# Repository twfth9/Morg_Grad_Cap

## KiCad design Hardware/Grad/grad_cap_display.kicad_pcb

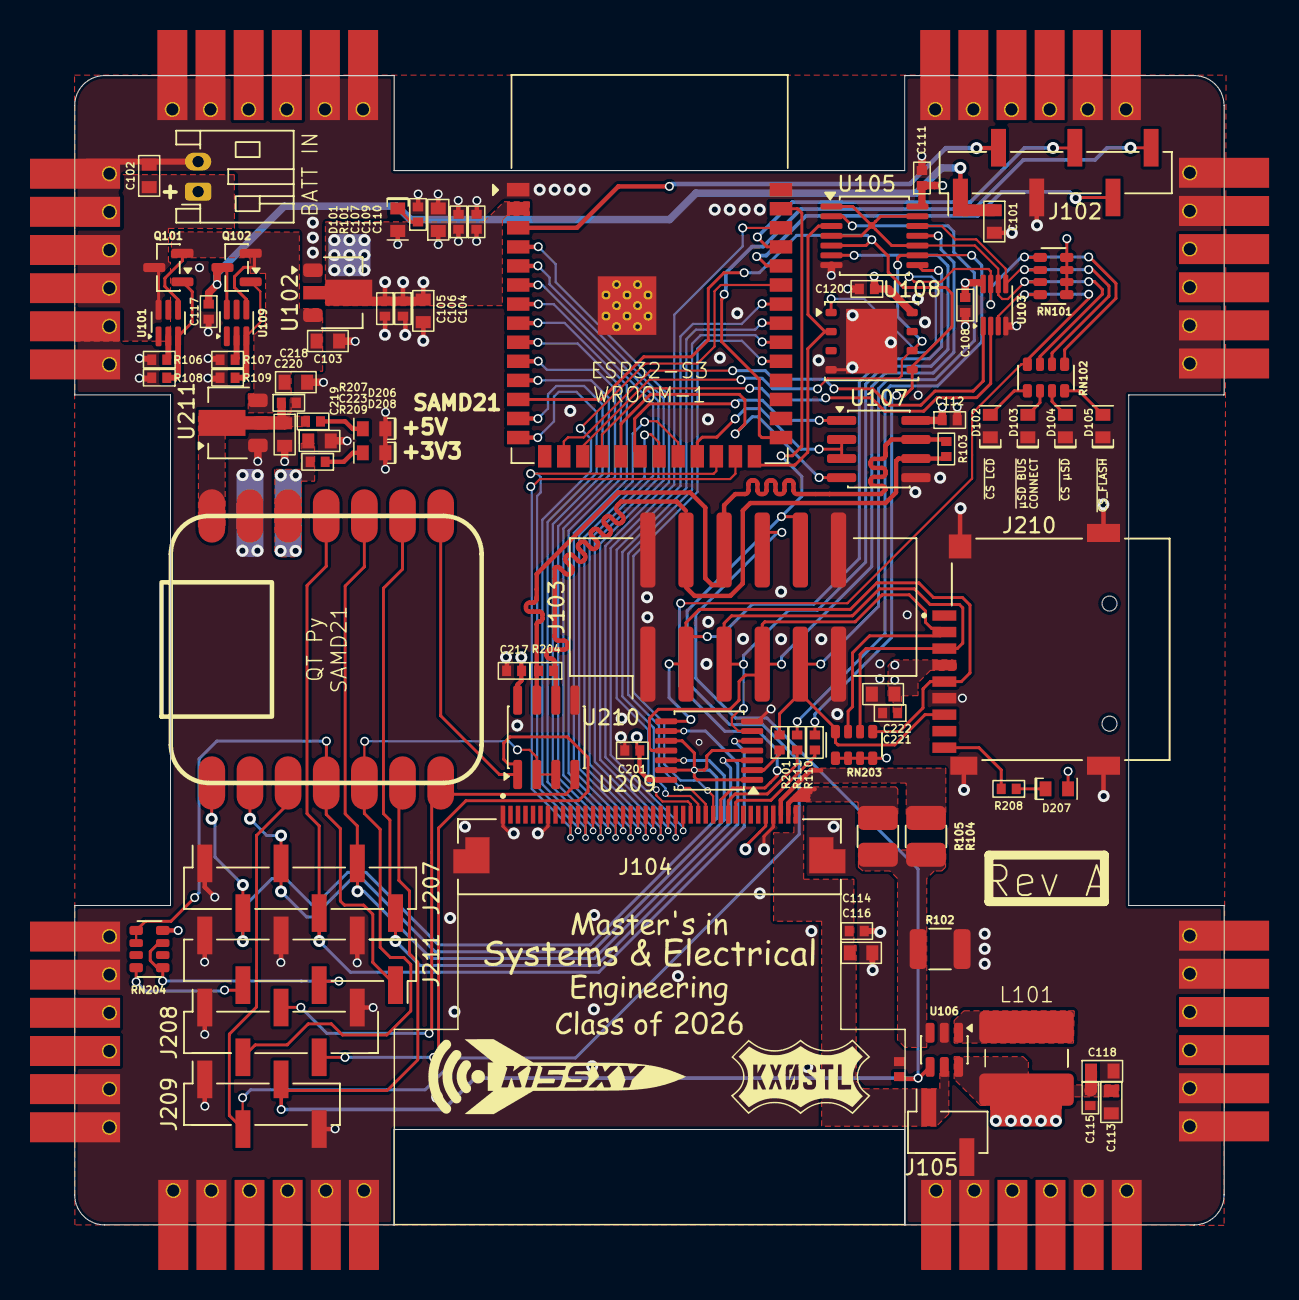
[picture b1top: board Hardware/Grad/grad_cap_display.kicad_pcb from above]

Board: 4 copper layers, 76.5 x 76.5 mm, 86 parts (0 on the bottom side), 83 nets.

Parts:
C101, C102, C103, C104, C107, C113, C116, C118, C218, C219, C222, C223: 22uF; Worthington_C_0603
C105, C106, C108, C109, C110, C111, C112, C114, C115, C117, C120, C201, C217, C220, C221: 100nF; Worthington_C_0402
C119: Worthington_C_0402
D101, D102, D103, D104, D105, D206, D207, D208: RED; Worthington_LED_0603
J101: Power In; JST_PH_S2B-PH-K_1x02_P2.00mm_Horizontal
J102: 6-Pos 2.54mm Header; PinHeader_1x06_P2.54mm_Vertical_SMD_Pin1Left
J103: 2x8 2.54mm IDC Header; IDC-Header_2x06_P2.54mm_Vertical_SMD
J104: Amphenol 40-Pin FPC; AMPHENOL_62684-402100ALF
J105: LCD Power TestPoint; PinHeader_1x02_P2.54mm_Vertical_SMD_Pin1Right
J207: SPI TestPoint; PinHeader_1x06_P2.54mm_Vertical_SMD_Pin1Right
J208: RS485 TestPoint; PinHeader_1x05_P2.54mm_Vertical_SMD_Pin1Right
J209: Extra TestPoint; PinHeader_1x04_P2.54mm_Vertical_SMD_Pin1Right
J210: Micro_SD_Card; CUI_MSD-4-A
J211: Push Button Header; PinHeader_1x06_P2.54mm_Vertical_SMD_Pin1Right
J401, J402, J403, J404: 01x30 Pads; PinSocket_1x30_P2.54mm_Vertical
L101: 22uH; CDRH5D28
Q101, Q102: DMP2045U; SOT-23
R101, R209: 430; Worthington_R_0402
R102, R104, R105: 10; R_1210_3225Metric
R103, R204: 120; Worthington_R_0402
R106, R107: 100k; Worthington_R_0402
R108, R109: 1M; Worthington_R_0402
R110, R111, R201: 100; Worthington_R_0402
R207, R208: 1k; Worthington_R_0402
RN101, RN204: 10k; RESCAXE80P320X160X70-8N
RN102: 430; RESCAXE80P320X160X70-8N
RN203: 47k; RESCAXE80P320X160X70-8N
U101, U109: DZDH0401DW; SOT-363_SC-70-6
U102, U211: AZ1117-5.0; SOT-89-3
U103: SN74LVC1G139; VSSOP-8_2.3x2mm_P0.5mm
U104: ESP32-S3-WROOM-1-N8R8; ESP32-S3-WROOM-1
U105, U209: TC7MBL3126CFT; TSSOP-14_4.4x5mm_P0.65mm
U106: AP3019AKTTR; TSOT-23-6
U107, U210: THVD1400D; SOIC-8_3.9x4.9mm_P1.27mm
U108: W25Q128JVP; WSON-8-1EP_6x5mm_P1.27mm_EP3.4x4.3mm
U212: QTPy SAMD21; Py_QT_SAMD21

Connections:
/+3V3: C104.1, C105.1, C106.1, C107.1, C108.1, C109.1, C110.1, C111.1, C112.1, C120.1, D101.2 (A), J104.36 (VDD), RN101.1 (4), RN101.2, RN101.3, RN101.4, U102.2 (VO), U103.8 (VCC), U104.2 (3V3), U105.14 (VCC), U107.8 (VCC), U108.8 (VCC)
/BACKLIGHT_PWM: C119.1, J103.8, J209.3, U106.4 (CTRL), U212.6 (SCL)
/BATT_IN: C102.1, C113.1, C115.1, C118.1, J101.1, J401.5, J401.6, J401.25, J401.26, J402.5, J402.6, J402.25, J402.26, J403.5, J403.6, J403.25, J403.26, J404.5, J404.6, J404.25, J404.26, L101.1, Q101.3 (D), U101.6 (DRAIN), U106.6 (V_{IN})
/BUTTON_SENSE: J211.1, RN204.1 (4), RN204.2, U212.4 (A3)
/ESP_CS0: U103.1 (A), U104.16 (IO46)
/ESP_CS1: U103.2 (B), U104.18 (IO10)
/ESP_CS_FLASH: RN101.5, RN102.5, U103.7 (Y0), U108.1 (~CS)
/ESP_CS_LCD: J104.30 (CS), RN101.8, RN102.8, U103.3 (Y3)
/ESP_CS_µSD: RN101.6, RN102.6, U103.5 (Y2), U105.12 (A4)
/ESP_MISO: U104.26 (IO45), U105.3 (B1), U108.2 (DO/IO_{1})
/ESP_MOSI: R110.1, U104.12 (IO8), U105.5 (A2), U108.5 (DI/IO_{0})
/ESP_MOSI_T: J104.32 (SDA), R110.2
/ESP_PROG_EN: J102.2, U104.3 (EN)
/ESP_PROG_IO0: J102.6, U104.27 (IO0)
/ESP_PROG_PWR: C101.1, C117.1, J102.1, Q102.3 (D), U109.6 (DRAIN)
/ESP_PROG_RXD0: J102.5, U104.36 (RXD0)
/ESP_PROG_TXD0: J102.4, U104.37 (TXD0)
/ESP_SCK: R111.1, U104.17 (IO9), U105.9 (A3), U108.6 (CLK)
/ESP_SCK_T: J104.31 (SCK), R111.2
/ESP_µSD_BUS_CONNECT: RN101.7 (5), RN102.7 (5), U103.6 (Y1), U105.1 (1~OE), U105.4 (2~OE), U105.10 (3~OE), U105.13 (4~OE)
/FRAME_SYNC: J103.10, J209.2, U104.39 (IO1), U212.3 (A2)
/LCD_RGB_DB0: J104.25 (DB0), U104.38 (IO2)
/LCD_RGB_DB1: J104.24 (DB1), U104.4 (IO4)
/LCD_RGB_DB2: J104.23 (DB2), U104.5 (IO5)
/LCD_RGB_DB3: J104.22 (DB3), U104.6 (IO6)
/LCD_RGB_DB4: J104.21 (DB4), U104.7 (IO7)
/LCD_RGB_DB5: J104.20 (DB5), U104.21 (IO13)
/LCD_RGB_DB6: J104.19 (DB6), U104.22 (IO14)
/LCD_RGB_DB7: J104.18 (DB7), U104.8 (IO15)
/LCD_RGB_DB8: J104.17 (DB8), U104.9 (IO16)
/LCD_RGB_DB9: J104.16 (DB9), U104.10 (IO17)
/LCD_RGB_DB10: J104.15 (DB10), U104.11 (IO18)
/LCD_RGB_DB11: J104.14 (DB11), U104.13 (USB_D-)
/LCD_RGB_DB12: J104.13 (DB12), U104.14 (USB_D+)
/LCD_RGB_DB13: J104.12 (DB13), U104.35 (IO42)
/LCD_RGB_DB14: J104.11 (DB14), U104.24 (IO47)
/LCD_RGB_DB15: J104.10 (DB15), U104.25 (IO48)
/LCD_RGB_DE: J104.28 (DE), U104.32 (IO39)
/LCD_RGB_HSYNC: J104.26 (HS), U104.34 (IO41)
/LCD_RGB_PCLK: J104.29 (PCLK), U104.31 (IO38)
/LCD_RGB_VSYNC: J104.27 (VS), U104.33 (IO40)
/PWR_IN: C103.1, C218.1, Q101.2 (S), Q102.2 (S), U101.4 (SOURCE), U102.3 (VI), U109.4 (SOURCE), U211.3 (VI)
/RS485_A: J103.4, R103.1, R204.1, U107.6 (A), U210.6 (A)
/RS485_B: J103.6, R103.2, R204.2, U107.7 (B), U210.7 (B)
/SAMD21_3V3: C201.1, C217.1, C221.1, C222.1, C223.1, D207.2 (A), J210.4 (VDD), R209.2, RN203.1 (4), RN203.2, RN203.3, RN203.4, RN204.8, U209.14 (VCC), U210.8 (VCC), U212.12 (3V)
/SAMD21_5V: C219.1, C220.1, R207.2, U211.2 (VO), U212.14 (5V)
/SAMD_CS_µSD: J207.3, U209.12 (A4), U212.2 (A1)
/SAMD_MISO: J207.5, U209.3 (B1), U212.10 (MI)
/SAMD_MOSI: J207.4, U209.5 (A2), U212.11 (MO)
/SAMD_SCK: J207.6, U209.9 (A3), U212.9 (SCK)
/SAMD_UART-RS485_DE: J208.2, U210.2 (~RE), U210.3 (DE), U212.5 (SDA)
/SAMD_UART-RS485_RX: J208.4, U210.1 (RO), U212.8 (RX)
/SAMD_UART-RS485_TX: J208.3, U210.4 (DI), U212.7 (TX)
/SAMD_µSD_BUS_CONNECT: J207.2, U209.1 (1~OE), U209.4 (2~OE), U209.10 (3~OE), U209.13 (4~OE), U212.1 (A0)
/UART-RS485_RX: U104.20 (IO12), U107.1 (RO)
/UART-RS485_TX: U104.19 (IO11), U107.4 (DI)
/UART_RS485_DE: U104.23 (IO21), U107.2 (~RE), U107.3 (DE)
/µSD_SPI_CS: J103.7, J210.2 (DAT3/CD), RN203.7 (5), U105.11 (B4), U209.11 (B4)
/µSD_SPI_MISO: J103.9, J210.7 (DAT0), R201.2, RN203.8, U105.2 (A1)
/µSD_SPI_MISO_T: R201.1, U209.2 (A1)
/µSD_SPI_MOSI: J103.5, J210.3 (CMD), RN203.6, U105.6 (B2), U209.6 (B2)
/µSD_SPI_SCK: J103.3, J210.5 (CLK), RN203.5, U105.8 (B3), U209.8 (B3)
GND: C101.2, C102.2, C103.2, C104.2, C105.2, C106.2, C107.2, C108.2, C109.2, C110.2, C111.2, C112.2, C113.2, C114.2, C115.2, C116.2, C117.2, C118.2, C119.2, C120.2, C201.2, C217.2, C218.2, C219.2, C220.2, C221.2, C222.2, C223.2, D102.1 (K), D103.1 (K), D104.1 (K), D105.1 (K), D206.1 (K), D208.1 (K), J101.2, J102.3, J103.1, J103.2, J103.11, J103.12, J104.1 (GND), J104.7 (GND), J104.37 (GND), J104.S1 (M), J104.S2 (M), J105.2, J207.1, J208.1, J208.5, J209.1, J209.4, J210.6 (VSS), J210.9 (SHIELD), J211.2, J211.4, J211.6, J401.3, J401.4, J401.7, J401.8, J401.23, J401.24, J401.27, J401.28, J402.3, J402.4, J402.7, J402.8, J402.23, J402.24, J402.27, J402.28, J403.3, J403.4, J403.7, J403.8, J403.23, J403.24, J403.27, J403.28, J404.3, J404.4, J404.7, J404.8, J404.23, J404.24, J404.27, J404.28, R101.2, R102.2, R106.2, R107.2, R108.2, R109.2, U102.1 (GND), U103.4 (GND), U104.1 (GND), U104.40 (GND), U104.41 (GND), U105.7 (GND), U106.2 (GND), U107.5 (GND), U108.4 (GND), U108.9 (EP), U209.7 (GND), U210.5 (GND), U211.1 (GND), U212.13 (GND)
unnamed: D101.1 (K), R101.1
unnamed: D102.2 (A), RN102.1 (4)
unnamed: D103.2 (A), RN102.2
unnamed: D104.2 (A), RN102.3
unnamed: D105.2 (A), RN102.4
unnamed: D206.2 (A), R207.1
unnamed: D207.1 (K), R208.1
unnamed: D208.2 (A), R209.1
unnamed: C114.1, C116.1, J104.40 (LEDA), J105.1, U106.5 (V_{OUT})
unnamed: J104.38 (LEDK), R104.2
unnamed: J104.39 (LEDK), R105.2
unnamed: J210.CD (CHIP_DETECT), R208.2
unnamed: J211.3, RN204.5, RN204.7 (5)
unnamed: J211.5, RN204.4
unnamed: Q101.1 (G), R108.1, U101.3 (BIAS)
unnamed: Q102.1 (G), R109.1, U109.3 (BIAS)
unnamed: R106.1, U101.2 (REF)
unnamed: R102.1, R104.1, R105.1, U106.3 (FB)
unnamed: L101.2, U106.1 (SW)
unnamed: R107.1, U109.2 (REF)

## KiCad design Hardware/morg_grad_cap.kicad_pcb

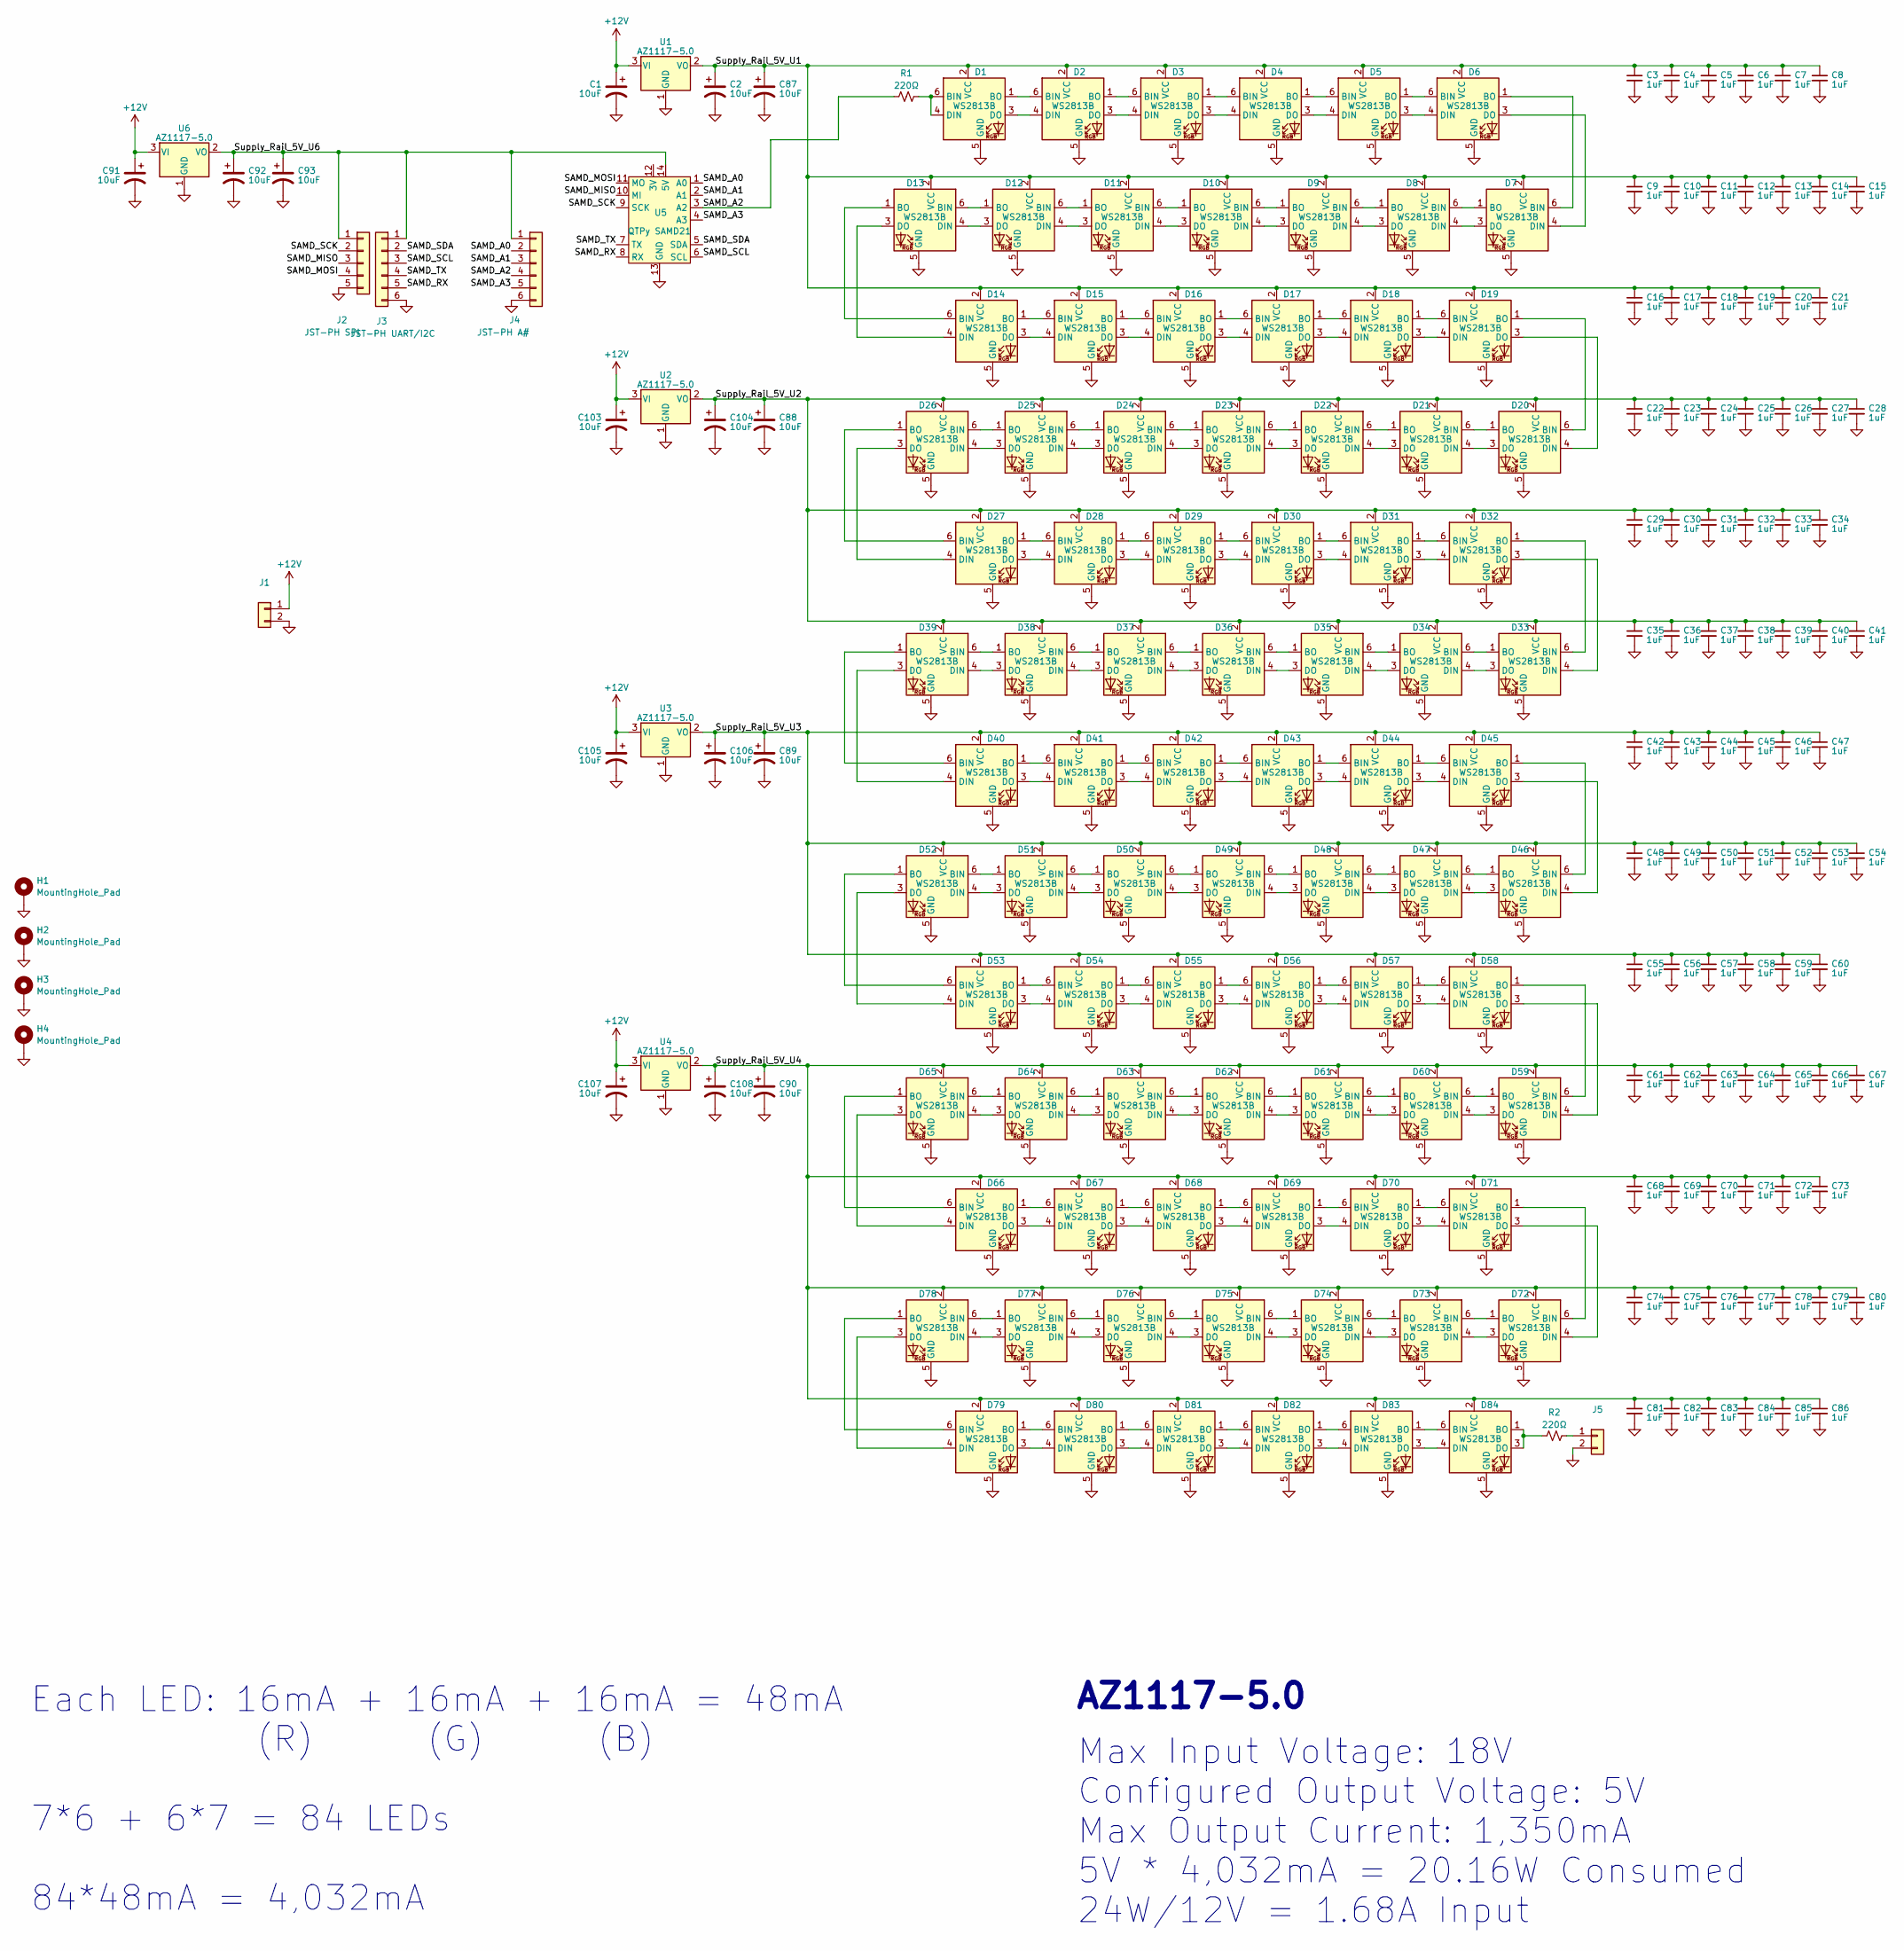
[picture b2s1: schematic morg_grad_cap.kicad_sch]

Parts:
C1, C2, C87, C88, C89, C90, C91, C92, C93, C103, C104, C105, C106, C107, C108: 10uF; C_0805_2012Metric_Pad1.18x1.45mm_HandSolder
C3, C4, C5, C6, C7, C8, C9, C10, C11, C12, C13, C14, C15, C16, C17, C18, C19, C20, C21, C22, C23, C24, C25, C26, C27, C28, C29, C30, C31, C32, C33, C34, C35, C36, C37, C38, C39, C40, C41, C42, C43, C44, C45, C46, C47, C48, C49, C50, C51, C52, C53, C54, C55, C56, C57, C58, C59, C60, C61, C62, C63, C64, C65, C66, C67, C68, C69, C70, C71, C72, C73, C74, C75, C76, C77, C78, C79, C80, C81, C82, C83, C84, C85, C86: 1uF; C_0603_1608Metric_Pad1.08x0.95mm_HandSolder
D1, D2, D3, D4, D5, D6, D7, D8, D9, D10, D11, D12, D13, D14, D15, D16, D17, D18, D19, D20, D21, D22, D23, D24, D25, D26, D27, D28, D29, D30, D31, D32, D33, D34, D35, D36, D37, D38, D39, D40, D41, D42, D43, D44, D45, D46, D47, D48, D49, D50, D51, D52, D53, D54, D55, D56, D57, D58, D59, D60, D61, D62, D63, D64, D65, D66, D67, D68, D69, D70, D71, D72, D73, D74, D75, D76, D77, D78, D79, D80, D81, D82, D83, D84: WS2813B; LED_WS2812_PLCC6_5.0x5.0mm_P1.6mm
H1, H2, H3, H4: MountingHole_Pad; MountingHole_3.2mm_M3_Pad
J1: JST-PH Batt Power In; JST_PH_S2B-PH-K_1x02_P2.00mm_Horizontal
J2: JST-PH SPI; JST_PH_S5B-PH-K_1x05_P2.00mm_Horizontal
J3: JST-PH UART/I2C; JST_PH_S6B-PH-K_1x06_P2.00mm_Horizontal
J4: JST-PH A#; JST_PH_S6B-PH-K_1x06_P2.00mm_Horizontal
J5: Data Out; JST_PH_S2B-PH-K_1x02_P2.00mm_Horizontal
R1, R2: 220Ω; R_0603_1608Metric_Pad0.98x0.95mm_HandSolder
U1, U2, U3, U4, U6: AZ1117-5.0; SOT-223-3_TabPin2
U5: QTPy SAMD21; Py_QT_SAMD21

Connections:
+12V: C1.1, C91.1, C103.1, C105.1, C107.1, J1.1, U1.3 (VI), U2.3 (VI), U3.3 (VI), U4.3 (VI), U6.3 (VI)
/SAMD_A0: J4.2, U5.1 (A0)
/SAMD_A1: J4.3, U5.2 (A1)
/SAMD_A2: J4.4, R1.1, U5.3 (A2)
/SAMD_A3: J4.5, U5.4 (A3)
/SAMD_MISO: J2.3, U5.10 (MI)
/SAMD_MOSI: J2.4, U5.11 (MO)
/SAMD_RX: J3.5, U5.8 (RX)
/SAMD_SCK: J2.2, U5.9 (SCK)
/SAMD_SCL: J3.3, U5.6 (SCL)
/SAMD_SDA: J3.2, U5.5 (SDA)
/SAMD_TX: J3.4, U5.7 (TX)
/Supply_Rail_5V_U1: C2.1, C3.1, C4.1, C5.1, C6.1, C7.1, C8.1, C9.1, C10.1, C11.1, C12.1, C13.1, C14.1, C15.1, C16.1, C17.1, C18.1, C19.1, C20.1, C21.1, C87.1, D1.2 (VCC), D2.2 (VCC), D3.2 (VCC), D4.2 (VCC), D5.2 (VCC), D6.2 (VCC), D7.2 (VCC), D8.2 (VCC), D9.2 (VCC), D10.2 (VCC), D11.2 (VCC), D12.2 (VCC), D13.2 (VCC), D14.2 (VCC), D15.2 (VCC), D16.2 (VCC), D17.2 (VCC), D18.2 (VCC), D19.2 (VCC), U1.2 (VO)
/Supply_Rail_5V_U2: C22.1, C23.1, C24.1, C25.1, C26.1, C27.1, C28.1, C29.1, C30.1, C31.1, C32.1, C33.1, C34.1, C35.1, C36.1, C37.1, C38.1, C39.1, C40.1, C41.1, C88.1, C104.1, D20.2 (VCC), D21.2 (VCC), D22.2 (VCC), D23.2 (VCC), D24.2 (VCC), D25.2 (VCC), D26.2 (VCC), D27.2 (VCC), D28.2 (VCC), D29.2 (VCC), D30.2 (VCC), D31.2 (VCC), D32.2 (VCC), D33.2 (VCC), D34.2 (VCC), D35.2 (VCC), D36.2 (VCC), D37.2 (VCC), D38.2 (VCC), D39.2 (VCC), U2.2 (VO)
/Supply_Rail_5V_U3: C42.1, C43.1, C44.1, C45.1, C46.1, C47.1, C48.1, C49.1, C50.1, C51.1, C52.1, C53.1, C54.1, C55.1, C56.1, C57.1, C58.1, C59.1, C60.1, C89.1, C106.1, D40.2 (VCC), D41.2 (VCC), D42.2 (VCC), D43.2 (VCC), D44.2 (VCC), D45.2 (VCC), D46.2 (VCC), D47.2 (VCC), D48.2 (VCC), D49.2 (VCC), D50.2 (VCC), D51.2 (VCC), D52.2 (VCC), D53.2 (VCC), D54.2 (VCC), D55.2 (VCC), D56.2 (VCC), D57.2 (VCC), D58.2 (VCC), U3.2 (VO)
/Supply_Rail_5V_U4: C61.1, C62.1, C63.1, C64.1, C65.1, C66.1, C67.1, C68.1, C69.1, C70.1, C71.1, C72.1, C73.1, C74.1, C75.1, C76.1, C77.1, C78.1, C79.1, C80.1, C81.1, C82.1, C83.1, C84.1, C85.1, C86.1, C90.1, C108.1, D59.2 (VCC), D60.2 (VCC), D61.2 (VCC), D62.2 (VCC), D63.2 (VCC), D64.2 (VCC), D65.2 (VCC), D66.2 (VCC), D67.2 (VCC), D68.2 (VCC), D69.2 (VCC), D70.2 (VCC), D71.2 (VCC), D72.2 (VCC), D73.2 (VCC), D74.2 (VCC), D75.2 (VCC), D76.2 (VCC), D77.2 (VCC), D78.2 (VCC), D79.2 (VCC), D80.2 (VCC), D81.2 (VCC), D82.2 (VCC), D83.2 (VCC), D84.2 (VCC), U4.2 (VO)
/Supply_Rail_5V_U6: C92.1, C93.1, J2.1, J3.1, J4.1, U5.14 (5V), U6.2 (VO)
GND: C1.2, C2.2, C3.2, C4.2, C5.2, C6.2, C7.2, C8.2, C9.2, C10.2, C11.2, C12.2, C13.2, C14.2, C15.2, C16.2, C17.2, C18.2, C19.2, C20.2, C21.2, C22.2, C23.2, C24.2, C25.2, C26.2, C27.2, C28.2, C29.2, C30.2, C31.2, C32.2, C33.2, C34.2, C35.2, C36.2, C37.2, C38.2, C39.2, C40.2, C41.2, C42.2, C43.2, C44.2, C45.2, C46.2, C47.2, C48.2, C49.2, C50.2, C51.2, C52.2, C53.2, C54.2, C55.2, C56.2, C57.2, C58.2, C59.2, C60.2, C61.2, C62.2, C63.2, C64.2, C65.2, C66.2, C67.2, C68.2, C69.2, C70.2, C71.2, C72.2, C73.2, C74.2, C75.2, C76.2, C77.2, C78.2, C79.2, C80.2, C81.2, C82.2, C83.2, C84.2, C85.2, C86.2, C87.2, C88.2, C89.2, C90.2, C91.2, C92.2, C93.2, C103.2, C104.2, C105.2, C106.2, C107.2, C108.2, D1.5 (GND), D2.5 (GND), D3.5 (GND), D4.5 (GND), D5.5 (GND), D6.5 (GND), D7.5 (GND), D8.5 (GND), D9.5 (GND), D10.5 (GND), D11.5 (GND), D12.5 (GND), D13.5 (GND), D14.5 (GND), D15.5 (GND), D16.5 (GND), D17.5 (GND), D18.5 (GND), D19.5 (GND), D20.5 (GND), D21.5 (GND), D22.5 (GND), D23.5 (GND), D24.5 (GND), D25.5 (GND), D26.5 (GND), D27.5 (GND), D28.5 (GND), D29.5 (GND), D30.5 (GND), D31.5 (GND), D32.5 (GND), D33.5 (GND), D34.5 (GND), D35.5 (GND), D36.5 (GND), D37.5 (GND), D38.5 (GND), D39.5 (GND), D40.5 (GND), D41.5 (GND), D42.5 (GND), D43.5 (GND), D44.5 (GND), D45.5 (GND), D46.5 (GND), D47.5 (GND), D48.5 (GND), D49.5 (GND), D50.5 (GND), D51.5 (GND), D52.5 (GND), D53.5 (GND), D54.5 (GND), D55.5 (GND), D56.5 (GND), D57.5 (GND), D58.5 (GND), D59.5 (GND), D60.5 (GND), D61.5 (GND), D62.5 (GND), D63.5 (GND), D64.5 (GND), D65.5 (GND), D66.5 (GND), D67.5 (GND), D68.5 (GND), D69.5 (GND), D70.5 (GND), D71.5 (GND), D72.5 (GND), D73.5 (GND), D74.5 (GND), D75.5 (GND), D76.5 (GND), D77.5 (GND), D78.5 (GND), D79.5 (GND), D80.5 (GND), D81.5 (GND), D82.5 (GND), D83.5 (GND), D84.5 (GND), H1.1, H2.1, H3.1, H4.1, J1.2, J2.5, J3.6, J4.6, J5.2, U1.1 (GND), U2.1 (GND), U3.1 (GND), U4.1 (GND), U5.13 (GND), U6.1 (GND)
unnamed: D1.4 (DIN), D1.6 (BIN), R1.2
unnamed: D1.1 (BO), D2.6 (BIN)
unnamed: D1.3 (DO), D2.4 (DIN)
unnamed: D2.1 (BO), D3.6 (BIN)
unnamed: D2.3 (DO), D3.4 (DIN)
unnamed: D3.1 (BO), D4.6 (BIN)
unnamed: D3.3 (DO), D4.4 (DIN)
unnamed: D4.1 (BO), D5.6 (BIN)
unnamed: D4.3 (DO), D5.4 (DIN)
unnamed: D5.1 (BO), D6.6 (BIN)
unnamed: D5.3 (DO), D6.4 (DIN)
unnamed: D6.1 (BO), D7.6 (BIN)
unnamed: D6.3 (DO), D7.4 (DIN)
unnamed: D7.1 (BO), D8.6 (BIN)
unnamed: D7.3 (DO), D8.4 (DIN)
unnamed: D8.1 (BO), D9.6 (BIN)
unnamed: D8.3 (DO), D9.4 (DIN)
unnamed: D9.1 (BO), D10.6 (BIN)
unnamed: D10.1 (BO), D11.6 (BIN)
unnamed: D9.3 (DO), D10.4 (DIN)
unnamed: D10.3 (DO), D11.4 (DIN)
unnamed: D11.1 (BO), D12.6 (BIN)
unnamed: D11.3 (DO), D12.4 (DIN)
unnamed: D12.1 (BO), D13.6 (BIN)
unnamed: D12.3 (DO), D13.4 (DIN)
unnamed: D13.1 (BO), D14.6 (BIN)
unnamed: D13.3 (DO), D14.4 (DIN)
unnamed: D14.1 (BO), D15.6 (BIN)
unnamed: D14.3 (DO), D15.4 (DIN)
unnamed: D15.1 (BO), D16.6 (BIN)
unnamed: D15.3 (DO), D16.4 (DIN)
unnamed: D16.1 (BO), D17.6 (BIN)
unnamed: D16.3 (DO), D17.4 (DIN)
unnamed: D17.1 (BO), D18.6 (BIN)
unnamed: D17.3 (DO), D18.4 (DIN)
unnamed: D18.1 (BO), D19.6 (BIN)
unnamed: D18.3 (DO), D19.4 (DIN)
unnamed: D19.1 (BO), D20.6 (BIN)
unnamed: D19.3 (DO), D20.4 (DIN)
unnamed: D20.1 (BO), D21.6 (BIN)
unnamed: D20.3 (DO), D21.4 (DIN)
unnamed: D21.1 (BO), D22.6 (BIN)
unnamed: D21.3 (DO), D22.4 (DIN)
unnamed: D22.1 (BO), D23.6 (BIN)
unnamed: D22.3 (DO), D23.4 (DIN)
unnamed: D23.1 (BO), D24.6 (BIN)
unnamed: D23.3 (DO), D24.4 (DIN)
unnamed: D24.1 (BO), D25.6 (BIN)
unnamed: D24.3 (DO), D25.4 (DIN)
unnamed: D25.1 (BO), D26.6 (BIN)
unnamed: D25.3 (DO), D26.4 (DIN)
unnamed: D26.1 (BO), D27.6 (BIN)
unnamed: D26.3 (DO), D27.4 (DIN)
unnamed: D27.1 (BO), D28.6 (BIN)
unnamed: D27.3 (DO), D28.4 (DIN)
unnamed: D28.1 (BO), D29.6 (BIN)
unnamed: D28.3 (DO), D29.4 (DIN)
unnamed: D29.1 (BO), D30.6 (BIN)
unnamed: D29.3 (DO), D30.4 (DIN)
unnamed: D30.1 (BO), D31.6 (BIN)
unnamed: D30.3 (DO), D31.4 (DIN)
unnamed: D31.1 (BO), D32.6 (BIN)
unnamed: D31.3 (DO), D32.4 (DIN)
unnamed: D32.1 (BO), D33.6 (BIN)
unnamed: D32.3 (DO), D33.4 (DIN)
unnamed: D33.1 (BO), D34.6 (BIN)
unnamed: D33.3 (DO), D34.4 (DIN)
unnamed: D34.1 (BO), D35.6 (BIN)
unnamed: D34.3 (DO), D35.4 (DIN)
unnamed: D35.1 (BO), D36.6 (BIN)
unnamed: D35.3 (DO), D36.4 (DIN)
unnamed: D36.1 (BO), D37.6 (BIN)
unnamed: D36.3 (DO), D37.4 (DIN)
unnamed: D37.1 (BO), D38.6 (BIN)
unnamed: D37.3 (DO), D38.4 (DIN)
unnamed: D38.1 (BO), D39.6 (BIN)
unnamed: D38.3 (DO), D39.4 (DIN)
unnamed: D39.1 (BO), D40.6 (BIN)
unnamed: D39.3 (DO), D40.4 (DIN)
unnamed: D40.1 (BO), D41.6 (BIN)
unnamed: D40.3 (DO), D41.4 (DIN)
unnamed: D41.1 (BO), D42.6 (BIN)
unnamed: D41.3 (DO), D42.4 (DIN)
unnamed: D42.1 (BO), D43.6 (BIN)
unnamed: D42.3 (DO), D43.4 (DIN)
unnamed: D43.1 (BO), D44.6 (BIN)
unnamed: D43.3 (DO), D44.4 (DIN)
unnamed: D44.1 (BO), D45.6 (BIN)
unnamed: D44.3 (DO), D45.4 (DIN)
unnamed: D45.1 (BO), D46.6 (BIN)
unnamed: D45.3 (DO), D46.4 (DIN)
unnamed: D46.1 (BO), D47.6 (BIN)
unnamed: D46.3 (DO), D47.4 (DIN)
unnamed: D47.1 (BO), D48.6 (BIN)
unnamed: D47.3 (DO), D48.4 (DIN)
unnamed: D48.1 (BO), D49.6 (BIN)
unnamed: D48.3 (DO), D49.4 (DIN)
unnamed: D49.1 (BO), D50.6 (BIN)
unnamed: D49.3 (DO), D50.4 (DIN)
unnamed: D50.1 (BO), D51.6 (BIN)
unnamed: D50.3 (DO), D51.4 (DIN)
unnamed: D51.1 (BO), D52.6 (BIN)
unnamed: D51.3 (DO), D52.4 (DIN)
unnamed: D52.1 (BO), D53.6 (BIN)
unnamed: D52.3 (DO), D53.4 (DIN)
unnamed: D53.1 (BO), D54.6 (BIN)
unnamed: D53.3 (DO), D54.4 (DIN)
unnamed: D54.1 (BO), D55.6 (BIN)
unnamed: D54.3 (DO), D55.4 (DIN)
unnamed: D55.1 (BO), D56.6 (BIN)
unnamed: D55.3 (DO), D56.4 (DIN)
unnamed: D56.1 (BO), D57.6 (BIN)
unnamed: D56.3 (DO), D57.4 (DIN)
unnamed: D57.1 (BO), D58.6 (BIN)
unnamed: D57.3 (DO), D58.4 (DIN)
unnamed: D58.1 (BO), D59.6 (BIN)
unnamed: D58.3 (DO), D59.4 (DIN)
unnamed: D59.1 (BO), D60.6 (BIN)
unnamed: D59.3 (DO), D60.4 (DIN)
unnamed: D60.1 (BO), D61.6 (BIN)
unnamed: D60.3 (DO), D61.4 (DIN)
unnamed: D61.1 (BO), D62.6 (BIN)
unnamed: D61.3 (DO), D62.4 (DIN)
unnamed: D62.1 (BO), D63.6 (BIN)
unnamed: D62.3 (DO), D63.4 (DIN)
unnamed: D63.1 (BO), D64.6 (BIN)
unnamed: D63.3 (DO), D64.4 (DIN)
unnamed: D64.1 (BO), D65.6 (BIN)
unnamed: D64.3 (DO), D65.4 (DIN)
unnamed: D65.1 (BO), D66.6 (BIN)
unnamed: D65.3 (DO), D66.4 (DIN)
unnamed: D66.1 (BO), D67.6 (BIN)
unnamed: D66.3 (DO), D67.4 (DIN)
unnamed: D67.1 (BO), D68.6 (BIN)
unnamed: D67.3 (DO), D68.4 (DIN)
unnamed: D68.1 (BO), D69.6 (BIN)
unnamed: D68.3 (DO), D69.4 (DIN)
unnamed: D69.1 (BO), D70.6 (BIN)
unnamed: D69.3 (DO), D70.4 (DIN)
unnamed: D70.1 (BO), D71.6 (BIN)
unnamed: D70.3 (DO), D71.4 (DIN)
unnamed: D71.1 (BO), D72.6 (BIN)
unnamed: D71.3 (DO), D72.4 (DIN)
unnamed: D72.1 (BO), D73.6 (BIN)
unnamed: D72.3 (DO), D73.4 (DIN)
unnamed: D73.1 (BO), D74.6 (BIN)
unnamed: D73.3 (DO), D74.4 (DIN)
unnamed: D74.1 (BO), D75.6 (BIN)
unnamed: D74.3 (DO), D75.4 (DIN)
unnamed: D75.1 (BO), D76.6 (BIN)
unnamed: D75.3 (DO), D76.4 (DIN)
unnamed: D76.1 (BO), D77.6 (BIN)
unnamed: D76.3 (DO), D77.4 (DIN)
unnamed: D77.1 (BO), D78.6 (BIN)
unnamed: D77.3 (DO), D78.4 (DIN)
unnamed: D78.1 (BO), D79.6 (BIN)
unnamed: D78.3 (DO), D79.4 (DIN)
unnamed: D79.1 (BO), D80.6 (BIN)
unnamed: D79.3 (DO), D80.4 (DIN)
unnamed: D80.1 (BO), D81.6 (BIN)
unnamed: D80.3 (DO), D81.4 (DIN)
unnamed: D81.1 (BO), D82.6 (BIN)
unnamed: D81.3 (DO), D82.4 (DIN)
unnamed: D82.1 (BO), D83.6 (BIN)
unnamed: D82.3 (DO), D83.4 (DIN)
unnamed: D83.1 (BO), D84.6 (BIN)
unnamed: D83.3 (DO), D84.4 (DIN)
unnamed: D84.1 (BO), D84.3 (DO), R2.1
unnamed: J5.1, R2.2

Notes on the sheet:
Each LED: 16mA + 16mA + 16mA = 48mA (R) (G) (B) 7*6 + 6*7 = 84 LEDs 84*48mA = 4,032mA
Max Input Voltage: 18V Configured Output Voltage: 5V Max Output Current: 1,350mA 5V * 4,032mA = 20.16W Consumed 24W/12V = 1.68A Input
AZ1117-5.0

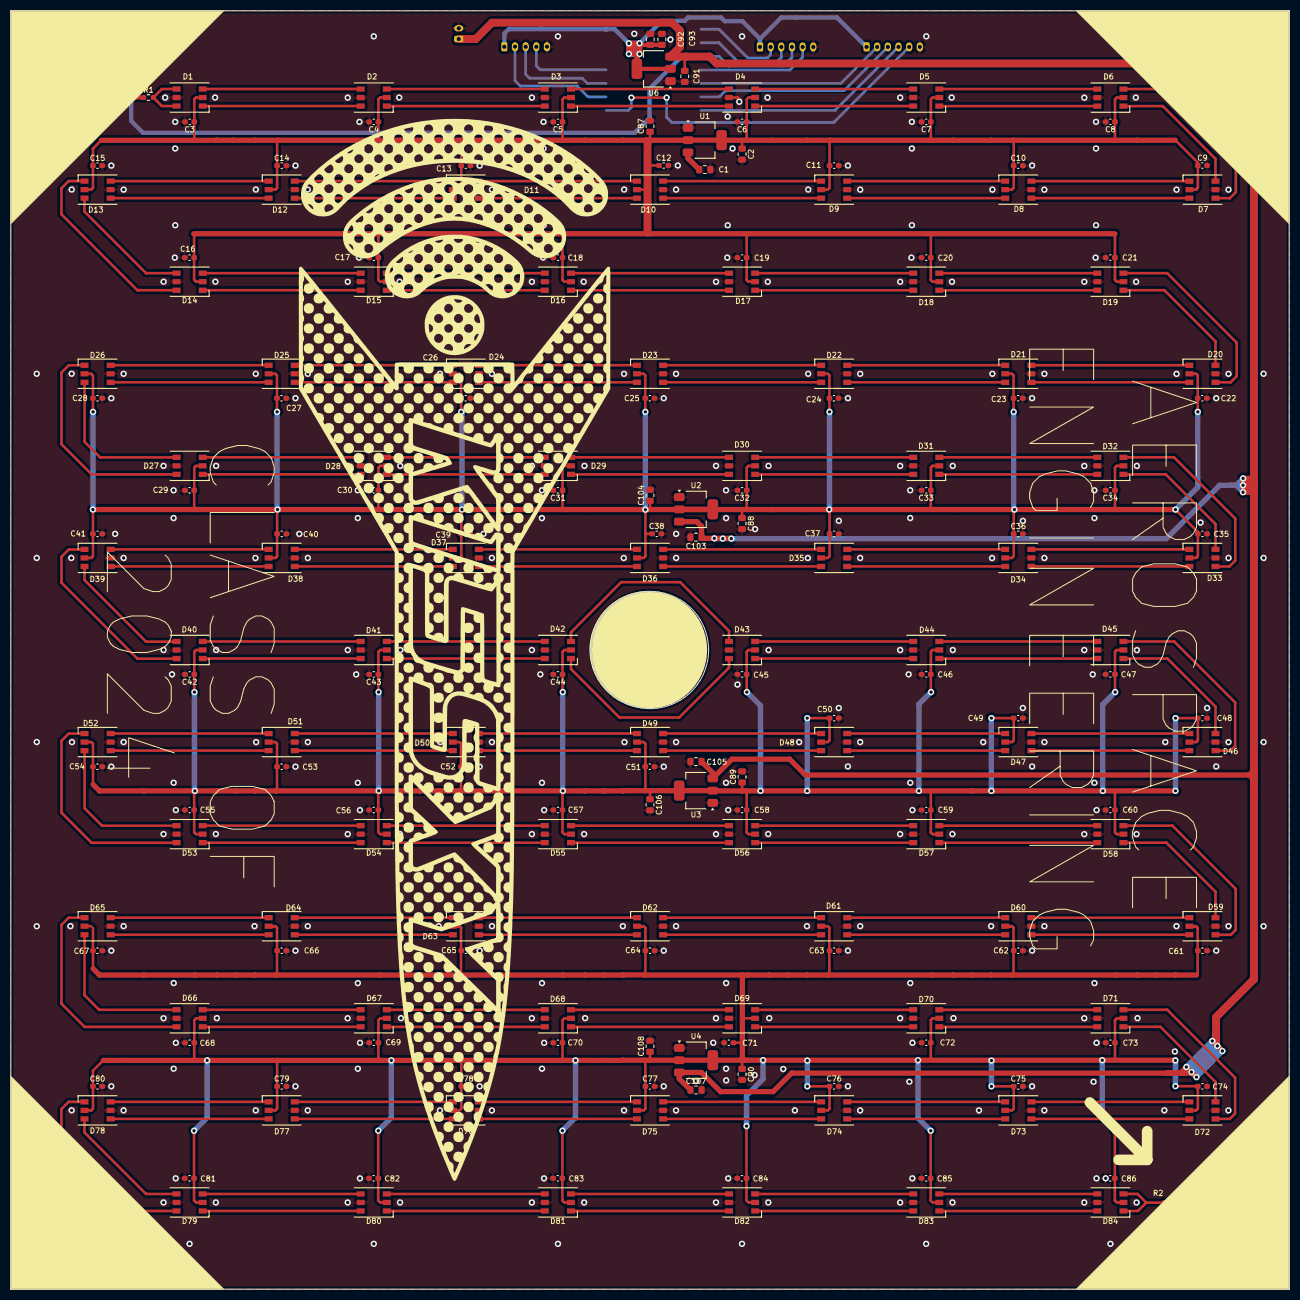
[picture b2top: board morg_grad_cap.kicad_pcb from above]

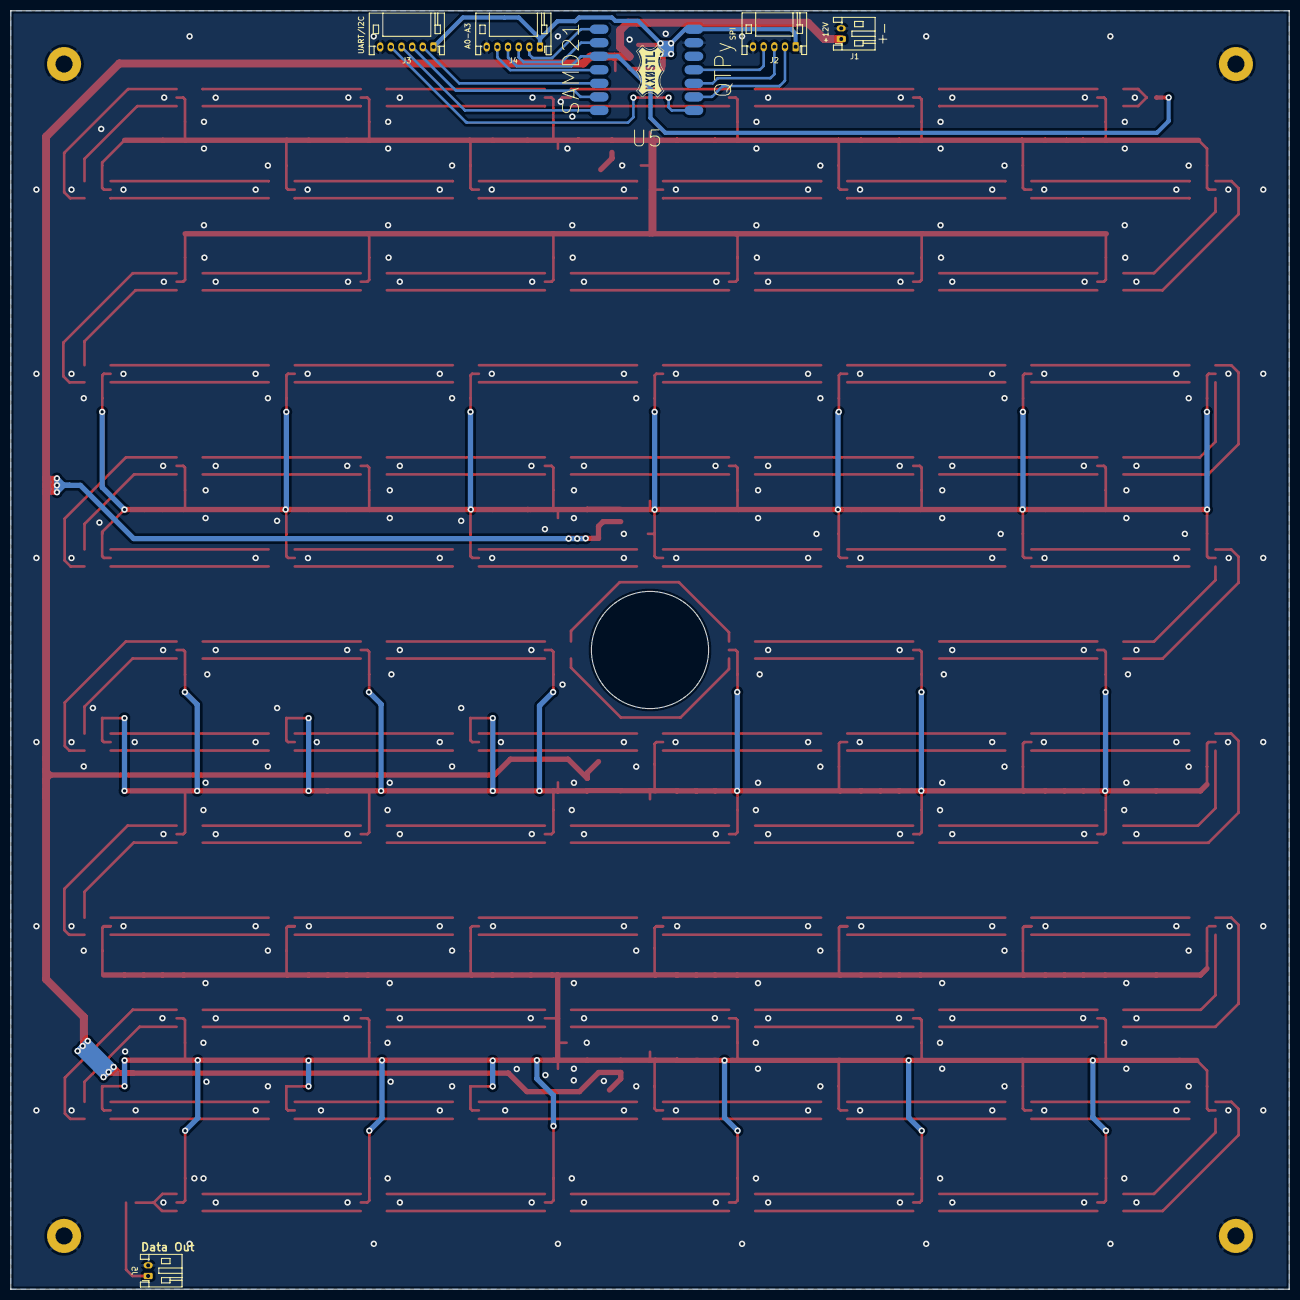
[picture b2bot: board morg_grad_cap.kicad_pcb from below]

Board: 2 copper layers, 240.0 x 240.0 mm, 200 parts (6 on the bottom side), 187 nets.
